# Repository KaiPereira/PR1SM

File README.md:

# PR1SM - Stacked Acrylic Keyboard

PR1SM is a minimalistic, stacked acrylic keyboard with neopixel backlight, running on KMK. It's built on a cheap, compact 2 layer PCB and has a fully fledged TKL (tenkeyless) layout.

## Custom Features
- Fully laser cut stacked case that will leak the RGB colors
- Full sized TKL (tenkeyless) layout with a function row
- Complete RGBA backlight on every single key with a power neopixel
- Decoupling caps, and stabilizing resistors for smooth power
- Simply runs off of a Raspberry Pi Pico
- Exposed black silkscreen design on a white PCB

## CAD Design

I used Onshape to design my keyboard like all of my projects. It was a bit tricky, because everything needed to be stock size and was going to be laser cut, so I couldn't have like partially cut in designs that a 3D printer could accomplish.

Anyways the entire case is just held together using M3 screws and it's all stacked so it should be decently rigid. The acrylic will let all the colors through, and it'll look sick.

*The silkscreen is actually black as shown in the render*

The case is separated into 5 separate laser cut pieces, respectively 3 - 3.5mm, 1 - 1.5mm and 1 - 5mm plate so it's relatively thin and pretty easy to assemble. [Onshape Link](https://cad.onshape.com/documents/8b572caa0e2769c057d91df7/w/f3c5c8a5f25f2593dceb7e8f/e/dc4500617840d95f6da4efee?renderMode=0&leftPanel=false&uiState=687a14d121cd8749fec3b29b)

## PCB Design

I designed the entire PCB in KiCad. I tried to stick to all best practices and the neopixels have decoupling and a resistor to smooth voltage. The keys are just a simple key matrix, and the MCU is a Pi Pico. I used the KiCad image converter to do the images, and some of them are drawn by me, others are AI generated and then there's some taken from the internet.

Now the PCB is a bit interesting, because it uses a ground fill on the bottom, and then a power fill on the top, the back lines run horizontally, while the front traces run vertically. Via's are on all the neopixel power lines for the fill with the decoupling caps right beside them.

Some 3D photo's:

## Firmware

PR1SM uses KMK firmware which is written in Python. I programmed all the keys in a matrix and then the backlit neopixels are just running in a wave pattern.

## Bill of Materials (BOM)
Here's everything you'll need to build your own PR1SM keyboard:

| Part                           | Price | Link                                                                                                                                                                                                                                                                                                                                                                                                                                                                                        |
| ------------------------------ | ----- | ------------------------------------------------------------------------------------------------------------------------------------------------------------------------------------------------------------------------------------------------------------------------------------------------------------------------------------------------------------------------------------------------------------------------------------------------------------------------------------------- |
| 89x Cherry MX Switches         | $25   | [Switches](https://www.aliexpress.com/item/1005006255961111.html?spm=a2g0o.productlist.main.1.313aZQHbZQHbyF&algo_pvid=6d1afddf-9989-4a7c-ad5a-14945d9acb3d&algo_exp_id=6d1afddf-9989-4a7c-ad5a-14945d9acb3d-0&pdp_ext_f=%7B%22order%22%3A%221044%22%2C%22eval%22%3A%221%22%7D&pdp_npi=4%40dis%21CAD%218.99%211.39%21%21%2145.94%217.11%21%402101d9ee17529990794214549e88c5%2112000036489552472%21sea%21CA%210%21ABX&curPageLogUid=JNMqebzd3gPt&utparam-url=scene%3Asearch%7Cquery_from%3A) |
| 89x Keycaps for a TKL keyboard | $30   | [Keycaps](https://www.amazon.ca/White-Keycaps-Minimalist-Mechanical-Keyboards/dp/B0BZCB56T5)                                                                                                                                                                                                                                                                                                                                                                                                |
| 90x SK6812 Mini-E LED's        | $30   | [Neopixels](https://lcsc.com/product-detail/Light-Emitting-Diodes-LED_OPSCO-Optoelectronics-SK6812MINI-E_C5149201.html)                                                                                                                                                                                                                                                                                                                                                                     |
| 1x Raspberry Pi Pico           | $7    | [Pi Pico](https://www.pishop.ca/product/raspberry-pi-pico-h-pre-soldered-headers/)                                                                                                                                                                                                                                                                                                                                                                                                          |
| 3x 3.5mm thick acrylic panels  | Free  | Uni will provide                                                                                                                                                                                                                                                                                                                                                                                                                                                                            |
| 1x 5mm thick acrylic panel     | Free  | Uni will provide                                                                                                                                                                                                                                                                                                                                                                                                                                                                            |
| 1x 1.5mm thick acrylic panel   | Free  | Uni will provide                                                                                                                                                                                                                                                                                                                                                                                                                                                                            |
| 10x Low profile M3 bolts/nuts  | ??    | Will find locally                                                                                                                                                                                                                                                                                                                                                                                                                                                                           |
| PCB                            | $50   | https://jlcpcb.com/                                                                                                                                                                                                                                                                                                                                                                                                                                                                         |

Total: Around **$142**

Here's the link to the spreadsheet: https://docs.google.com/spreadsheets/d/1PX1jr134__XBLFXCxBkakxo4KN2pxjdmwIgQ4_i7XN4/edit?usp=sharing

## Credits & Help

Thanks to @cheyao and the KiCad discord server for helping me with the wiring and the decoupling caps. @alcovesofastridpark on reddit for the main inspiration for the stacked acrylic and backlight. And of course @qcoral and @acornitum for starting Highway, the program funding this keyboard.

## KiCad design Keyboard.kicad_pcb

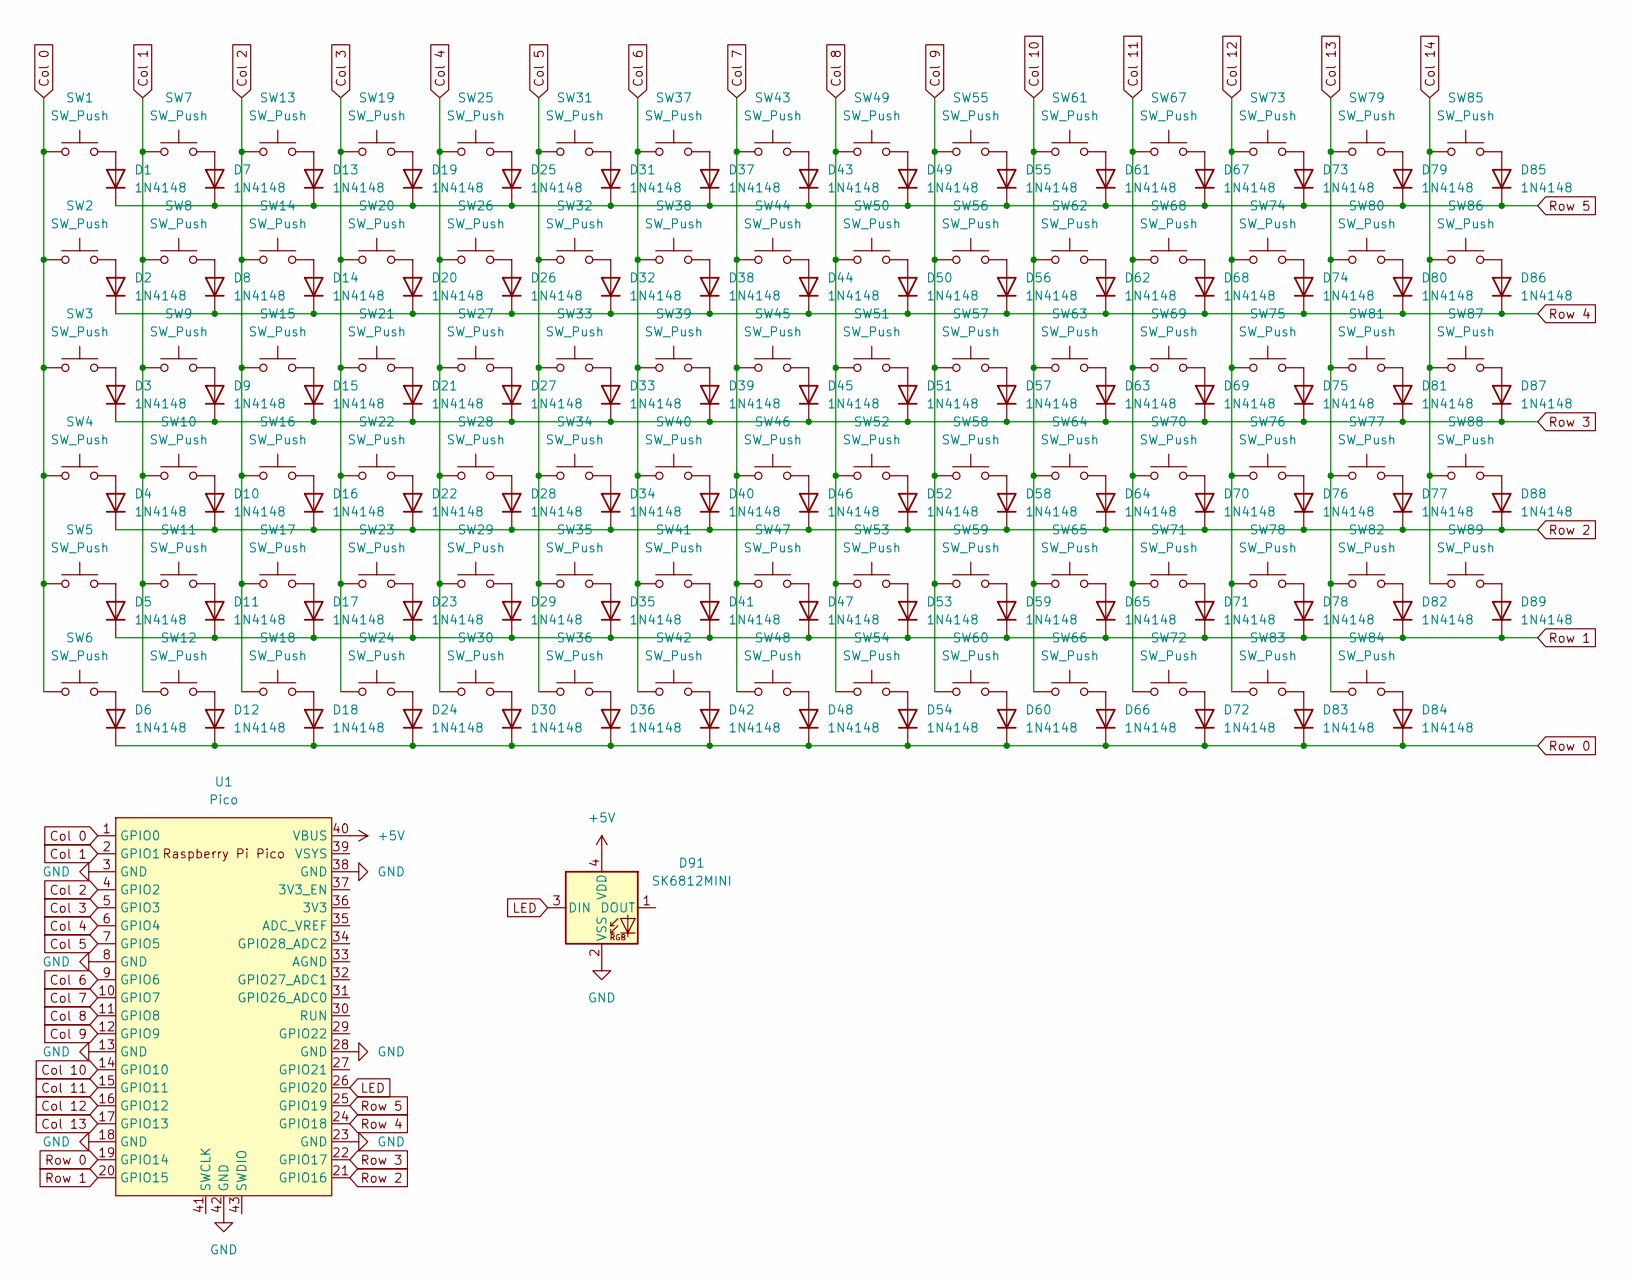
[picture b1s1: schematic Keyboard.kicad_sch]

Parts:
D1, D2, D3, D4, D5, D6, D7, D8, D9, D10, D11, D12, D13, D14, D15, D16, D17, D18, D19, D20, D21, D22, D23, D24, D25, D26, D27, D28, D29, D30, D31, D32, D33, D34, D35, D36, D37, D38, D39, D40, D41, D42, D43, D44, D45, D46, D47, D48, D49, D50, D51, D52, D53, D54, D55, D56, D57, D58, D59, D60, D61, D62, D63, D64, D65, D66, D67, D68, D69, D70, D71, D72, D73, D74, D75, D76, D77, D78, D79, D80, D81, D82, D83, D84, D85, D86, D87, D88, D89: 1N4148; D_DO-35_SOD27_P7.62mm_Horizontal
D91: SK6812MINI; LED_SK6812MINI_PLCC4_3.5x3.5mm_P1.75mm
SW1, SW2, SW7, SW8, SW9, SW10, SW11, SW13, SW14, SW15, SW16, SW17, SW19, SW20, SW21, SW22, SW23, SW25, SW26, SW27, SW28, SW29, SW31, SW32, SW33, SW34, SW35, SW37, SW38, SW39, SW40, SW41, SW43, SW44, SW45, SW46, SW47, SW49, SW50, SW51, SW52, SW53, SW54, SW55, SW56, SW57, SW58, SW59, SW60, SW61, SW62, SW63, SW64, SW65, SW66, SW67, SW68, SW69, SW70, SW72, SW73, SW74, SW75, SW77, SW78, SW79, SW82, SW83, SW84, SW85, SW86, SW87, SW88, SW89: SW_Push; SW_Cherry_MX_1.00u_PCB
SW3, SW81: SW_Push; SW_Cherry_MX_1.50u_PCB
SW4: SW_Push; SW_Cherry_MX_1.75u_PCB
SW5, SW76: SW_Push; SW_Cherry_MX_2.25u_PCB
SW6, SW12, SW18, SW24, SW36, SW42, SW48: SW_Push; SW_Cherry_MX_1.25u_PCB
SW30: SW_Push; SW_Cherry_MX_6.25u_PCB
SW71: SW_Push; SW_Cherry_MX_2.75u_PCB
SW80: SW_Push; SW_Cherry_MX_2.00u_PCB
U1: Pico; RaspberryPi_Pico_Common_THT

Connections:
+5V: D91.4 (VDD), U1.40 (VBUS)
Col 0: SW1.1, SW2.1, SW3.1, SW4.1, SW5.1, SW6.1, U1.1 (GPIO0)
Col 1: SW7.1, SW8.1, SW9.1, SW10.1, SW11.1, SW12.1, U1.2 (GPIO1)
Col 2: SW13.1, SW14.1, SW15.1, SW16.1, SW17.1, SW18.1, U1.4 (GPIO2)
Col 3: SW19.1, SW20.1, SW21.1, SW22.1, SW23.1, SW24.1, U1.5 (GPIO3)
Col 4: SW25.1, SW26.1, SW27.1, SW28.1, SW29.1, SW30.1, U1.6 (GPIO4)
Col 5: SW31.1, SW32.1, SW33.1, SW34.1, SW35.1, SW36.1, U1.7 (GPIO5)
Col 6: SW37.1, SW38.1, SW39.1, SW40.1, SW41.1, SW42.1, U1.9 (GPIO6)
Col 7: SW43.1, SW44.1, SW45.1, SW46.1, SW47.1, SW48.1, U1.10 (GPIO7)
Col 8: SW49.1, SW50.1, SW51.1, SW52.1, SW53.1, SW54.1, U1.11 (GPIO8)
Col 9: SW55.1, SW56.1, SW57.1, SW58.1, SW59.1, SW60.1, U1.12 (GPIO9)
Col 10: SW61.1, SW62.1, SW63.1, SW64.1, SW65.1, SW66.1, U1.14 (GPIO10)
Col 11: SW67.1, SW68.1, SW69.1, SW70.1, SW71.1, SW72.1, U1.15 (GPIO11)
Col 12: SW73.1, SW74.1, SW75.1, SW76.1, SW78.1, SW83.1, U1.16 (GPIO12)
Col 13: SW77.1, SW79.1, SW80.1, SW81.1, SW82.1, SW84.1, U1.17 (GPIO13)
Col 14: SW85.1, SW86.1, SW87.1, SW88.1, SW89.1
GND: D91.2 (VSS), U1.3 (GND), U1.8 (GND), U1.13 (GND), U1.18 (GND), U1.23 (GND), U1.28 (GND), U1.38 (GND), U1.42 (GND)
LED: D91.3 (DIN), U1.26 (GPIO20)
unnamed: D1.2 (A), SW1.2
unnamed: D2.2 (A), SW2.2
unnamed: D3.2 (A), SW3.2
unnamed: D4.2 (A), SW4.2
unnamed: D5.2 (A), SW5.2
unnamed: D6.2 (A), SW6.2
unnamed: D7.2 (A), SW7.2
unnamed: D8.2 (A), SW8.2
unnamed: D9.2 (A), SW9.2
unnamed: D10.2 (A), SW10.2
unnamed: D11.2 (A), SW11.2
unnamed: D12.2 (A), SW12.2
unnamed: D13.2 (A), SW13.2
unnamed: D14.2 (A), SW14.2
unnamed: D15.2 (A), SW15.2
unnamed: D16.2 (A), SW16.2
unnamed: D17.2 (A), SW17.2
unnamed: D18.2 (A), SW18.2
unnamed: D19.2 (A), SW19.2
unnamed: D20.2 (A), SW20.2
unnamed: D21.2 (A), SW21.2
unnamed: D22.2 (A), SW22.2
unnamed: D23.2 (A), SW23.2
unnamed: D24.2 (A), SW24.2
unnamed: D25.2 (A), SW25.2
unnamed: D26.2 (A), SW26.2
unnamed: D27.2 (A), SW27.2
unnamed: D28.2 (A), SW28.2
unnamed: D29.2 (A), SW29.2
unnamed: D30.2 (A), SW30.2
unnamed: D31.2 (A), SW31.2
unnamed: D32.2 (A), SW32.2
unnamed: D33.2 (A), SW33.2
unnamed: D34.2 (A), SW34.2
unnamed: D35.2 (A), SW35.2
unnamed: D36.2 (A), SW36.2
unnamed: D37.2 (A), SW37.2
unnamed: D38.2 (A), SW38.2
unnamed: D39.2 (A), SW39.2
unnamed: D40.2 (A), SW40.2
unnamed: D41.2 (A), SW41.2
unnamed: D42.2 (A), SW42.2
unnamed: D43.2 (A), SW43.2
unnamed: D44.2 (A), SW44.2
unnamed: D45.2 (A), SW45.2
unnamed: D46.2 (A), SW46.2
unnamed: D47.2 (A), SW47.2
unnamed: D48.2 (A), SW48.2
unnamed: D49.2 (A), SW49.2
unnamed: D50.2 (A), SW50.2
unnamed: D51.2 (A), SW51.2
unnamed: D52.2 (A), SW52.2
unnamed: D53.2 (A), SW53.2
unnamed: D54.2 (A), SW54.2
unnamed: D55.2 (A), SW55.2
unnamed: D56.2 (A), SW56.2
unnamed: D57.2 (A), SW57.2
unnamed: D58.2 (A), SW58.2
unnamed: D59.2 (A), SW59.2
unnamed: D60.2 (A), SW60.2
unnamed: D61.2 (A), SW61.2
unnamed: D62.2 (A), SW62.2
unnamed: D63.2 (A), SW63.2
unnamed: D64.2 (A), SW64.2
unnamed: D65.2 (A), SW65.2
unnamed: D66.2 (A), SW66.2
unnamed: D67.2 (A), SW67.2
unnamed: D68.2 (A), SW68.2
unnamed: D69.2 (A), SW69.2
unnamed: D70.2 (A), SW70.2
unnamed: D71.2 (A), SW71.2
unnamed: D72.2 (A), SW72.2
unnamed: D73.2 (A), SW73.2
unnamed: D74.2 (A), SW74.2
unnamed: D75.2 (A), SW75.2
unnamed: D76.2 (A), SW76.2
unnamed: D77.2 (A), SW77.2
unnamed: D78.2 (A), SW78.2
unnamed: D79.2 (A), SW79.2
unnamed: D80.2 (A), SW80.2
unnamed: D81.2 (A), SW81.2
unnamed: D82.2 (A), SW82.2
unnamed: D83.2 (A), SW83.2
unnamed: D84.2 (A), SW84.2
unnamed: D85.2 (A), SW85.2
unnamed: D86.2 (A), SW86.2
unnamed: D87.2 (A), SW87.2
unnamed: D88.2 (A), SW88.2
unnamed: D89.2 (A), SW89.2
Row 0: D6.1 (K), D12.1 (K), D18.1 (K), D24.1 (K), D30.1 (K), D36.1 (K), D42.1 (K), D48.1 (K), D54.1 (K), D60.1 (K), D66.1 (K), D72.1 (K), D83.1 (K), D84.1 (K), U1.19 (GPIO14)
Row 1: D5.1 (K), D11.1 (K), D17.1 (K), D23.1 (K), D29.1 (K), D35.1 (K), D41.1 (K), D47.1 (K), D53.1 (K), D59.1 (K), D65.1 (K), D71.1 (K), D78.1 (K), D82.1 (K), D89.1 (K), U1.20 (GPIO15)
Row 2: D4.1 (K), D10.1 (K), D16.1 (K), D22.1 (K), D28.1 (K), D34.1 (K), D40.1 (K), D46.1 (K), D52.1 (K), D58.1 (K), D64.1 (K), D70.1 (K), D76.1 (K), D77.1 (K), D88.1 (K), U1.21 (GPIO16)
Row 3: D3.1 (K), D9.1 (K), D15.1 (K), D21.1 (K), D27.1 (K), D33.1 (K), D39.1 (K), D45.1 (K), D51.1 (K), D57.1 (K), D63.1 (K), D69.1 (K), D75.1 (K), D81.1 (K), D87.1 (K), U1.22 (GPIO17)
Row 4: D2.1 (K), D8.1 (K), D14.1 (K), D20.1 (K), D26.1 (K), D32.1 (K), D38.1 (K), D44.1 (K), D50.1 (K), D56.1 (K), D62.1 (K), D68.1 (K), D74.1 (K), D80.1 (K), D86.1 (K), U1.24 (GPIO18)
Row 5: D1.1 (K), D7.1 (K), D13.1 (K), D19.1 (K), D25.1 (K), D31.1 (K), D37.1 (K), D43.1 (K), D49.1 (K), D55.1 (K), D61.1 (K), D67.1 (K), D73.1 (K), D79.1 (K), D85.1 (K), U1.25 (GPIO19)

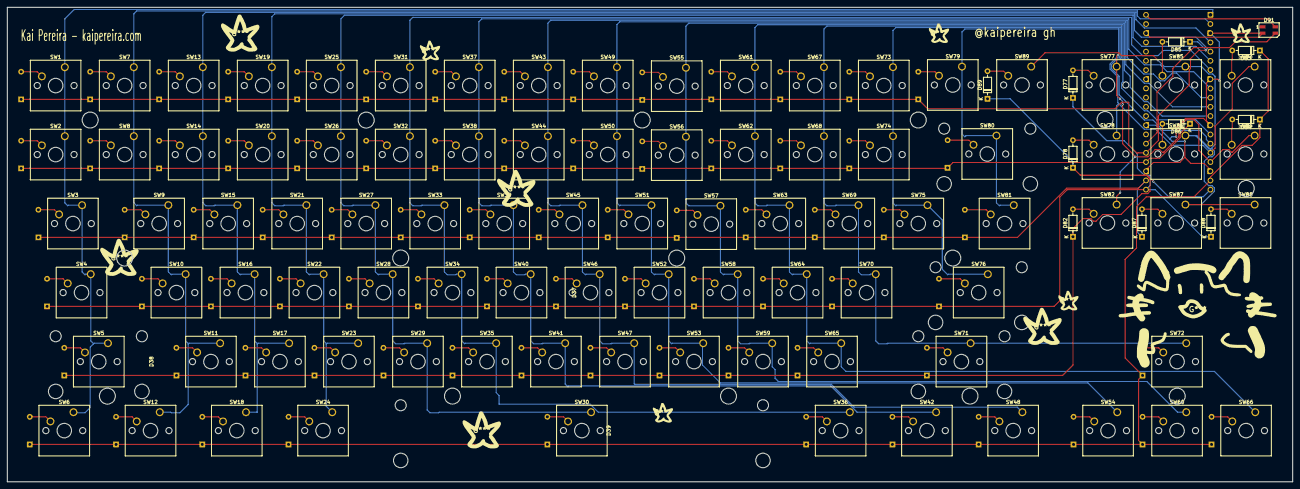
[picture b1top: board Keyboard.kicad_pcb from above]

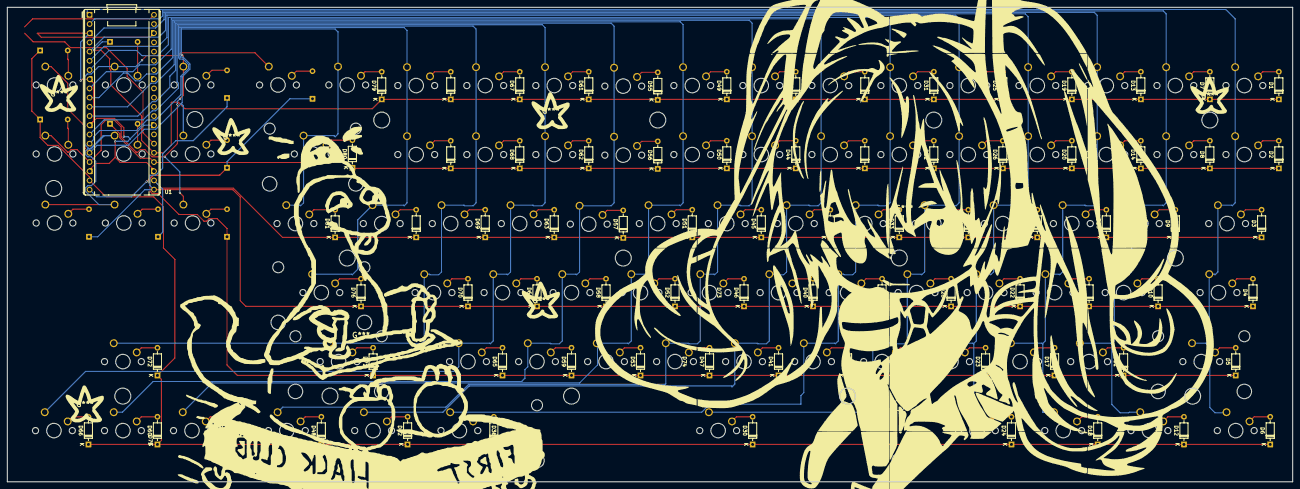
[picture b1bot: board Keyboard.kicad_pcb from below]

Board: 2 copper layers, 354.8 x 131.0 mm, 180 parts (80 on the bottom side), 113 nets.

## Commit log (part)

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2025-04-14 pcb files
2025-04-14 backup
2025-04-16 added holes to my pcb
2025-04-16 fix some drc errors
2025-04-16 some new stuff
2025-04-16 updated footprints, didnt rlly seem to work lol
2025-04-16 more footprint stuff
2025-04-17 some more pcb stuff
2025-04-24 updating pcb
2025-07-09 adding files
2025-07-09 fixed all drc errors on the pcb and optimize the power a bit more
2025-07-10 added 3d models to keys
2025-07-10 added silkscreen to PCB
2025-07-10 added new silkscreen to pcb
2025-07-10 Test
2025-07-10 added 3d model of keyboard
2025-07-10 adding some 3d models
2025-07-10 3d models and updated footprints
2025-07-10 rasp pi model
2025-07-16 some pcb stuff
2025-07-17 added journal and some other stuff
2025-07-18 updating the pcb and added the firmware file
2025-07-18 another pcb update
2025-07-18 working on journal and readme
2025-07-18 added the temporary readme
2025-07-18 added the CAD files
2025-07-18 added render and renaming some files
2025-07-18 added render file to lfs and renamed pcb folder
2025-07-18 adding render.blend via LFS
2025-07-19 updated the pcb and some blender stuff
2025-07-19 added blend1 file to lfs and some pcb stuff
2025-07-19 updated the journal a bit and some pcb stuff
2025-07-19 updated the blender file and also some pcb stuff
2025-07-19 adding somre more blender stuff
2025-07-19 adding in my HDRI and some more blender stuff
2025-07-19 forgot some blender stuff
2025-07-19 added HDRI to blender render
2025-07-19 did some case stuff for the render
2025-07-19 updating the render
2025-07-19 added new render and stuff
2025-07-19 actually moved the pcb now instead of animating
2025-07-19 updated render and did some more lender stuff
2025-07-19 finished writing journal
2025-07-20 some production files
2025-07-20 updated journal and added BOM
2025-07-20 added pcb photo's
2025-07-21 Added keycaps to BOM
2025-07-21 added firmware
2025-07-25 updated spreadsheet
2025-07-25 updated readme bom
2025-08-07 updating journal
2025-08-13 update readme with build
2025-08-13 fix image
2025-08-19 update with dxf's
2025-09-09 update journal
